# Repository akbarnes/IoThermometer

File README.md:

# IoThermometer
KiCAD PCB layout for a NodeMCU-based IoT thermometer to use with ESPHome

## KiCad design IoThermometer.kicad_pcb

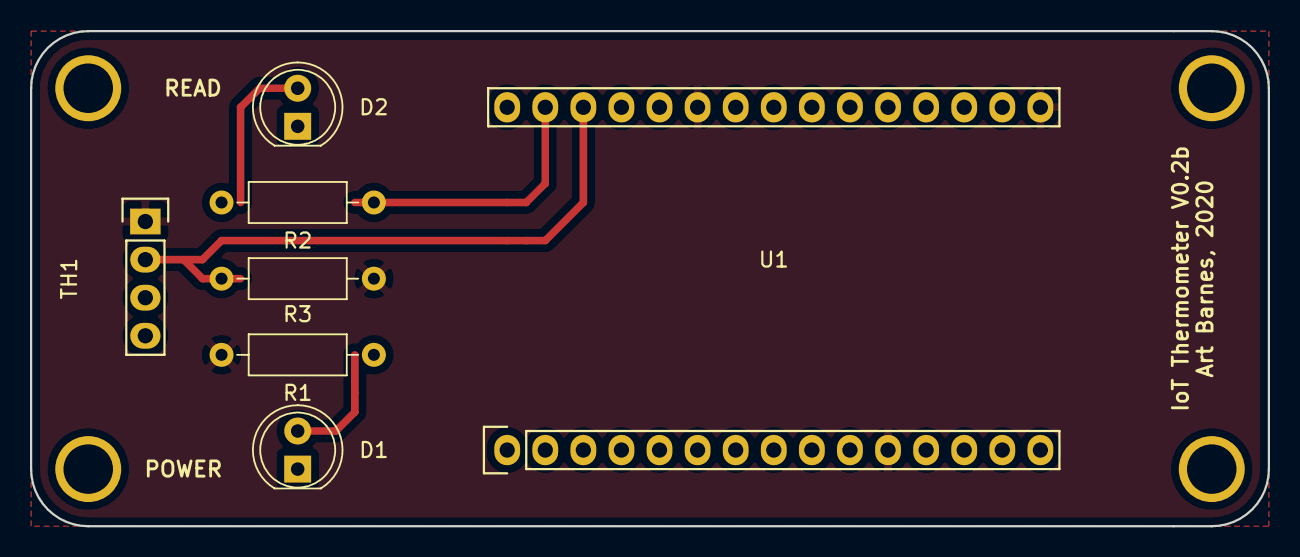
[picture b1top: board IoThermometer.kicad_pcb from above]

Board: 2 copper layers, 82.6 x 33.0 mm, 7 parts (0 on the bottom side), 6 nets.

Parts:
D1, D2: LED; LED_D5.0mm
R1, R2: 330; R_Axial_DIN0207_L6.3mm_D2.5mm_P10.16mm_Horizontal
R3: 4.7k; R_Axial_DIN0207_L6.3mm_D2.5mm_P10.16mm_Horizontal
TH1: DHT22_Temperature_Humidity
U1: NodeMCU_Amica_R2

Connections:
+3V3: R1.1, R3.1, TH1.1, U1.11, U1.16, U1.25
GND: D1.1, D2.1, TH1.4, U1.10, U1.14, U1.17, U1.24
unnamed: D1.2, R1.2
unnamed: D2.2, R2.1
unnamed: R2.2, U1.29
unnamed: R3.2, TH1.2, U1.28

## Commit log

2019-08-28 added libraries
2019-08-28 updated gitignore
2019-08-28 changed footprints to through-hole
2019-09-07 adjusted pcb size
2019-09-07 closed pcb outline
2020-01-11 edited silkscreen
2020-03-12 change dht22 symbol, fix pinout in footprint
2020-04-14 adjust layer visibility
2020-04-14 resize resistors & change about text
2020-04-14 adust layer visibility
2020-04-14 adjust project about data
